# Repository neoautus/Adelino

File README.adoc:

= Adelino
:page-layout: book

O Adelino é uma placa de desenvolvimento baseada no ATmega32U4 com um módulo ESP-12F integrado.
Ela foi inicialmente inspirada no Arduino Leonardo e no Arduino Yún.

Visite nosso https://github.com/neoautus/Adelino/wiki[Wiki] para conhecer melhor este produto!

'''

Adelino is an ATmega32U4 development board with integrated ESP-12F module.
It was initially inspired by Arduino Leonardo and Arduino Yún.

Visit our https://github.com/neoautus/Adelino/wiki[Wiki] for more information!

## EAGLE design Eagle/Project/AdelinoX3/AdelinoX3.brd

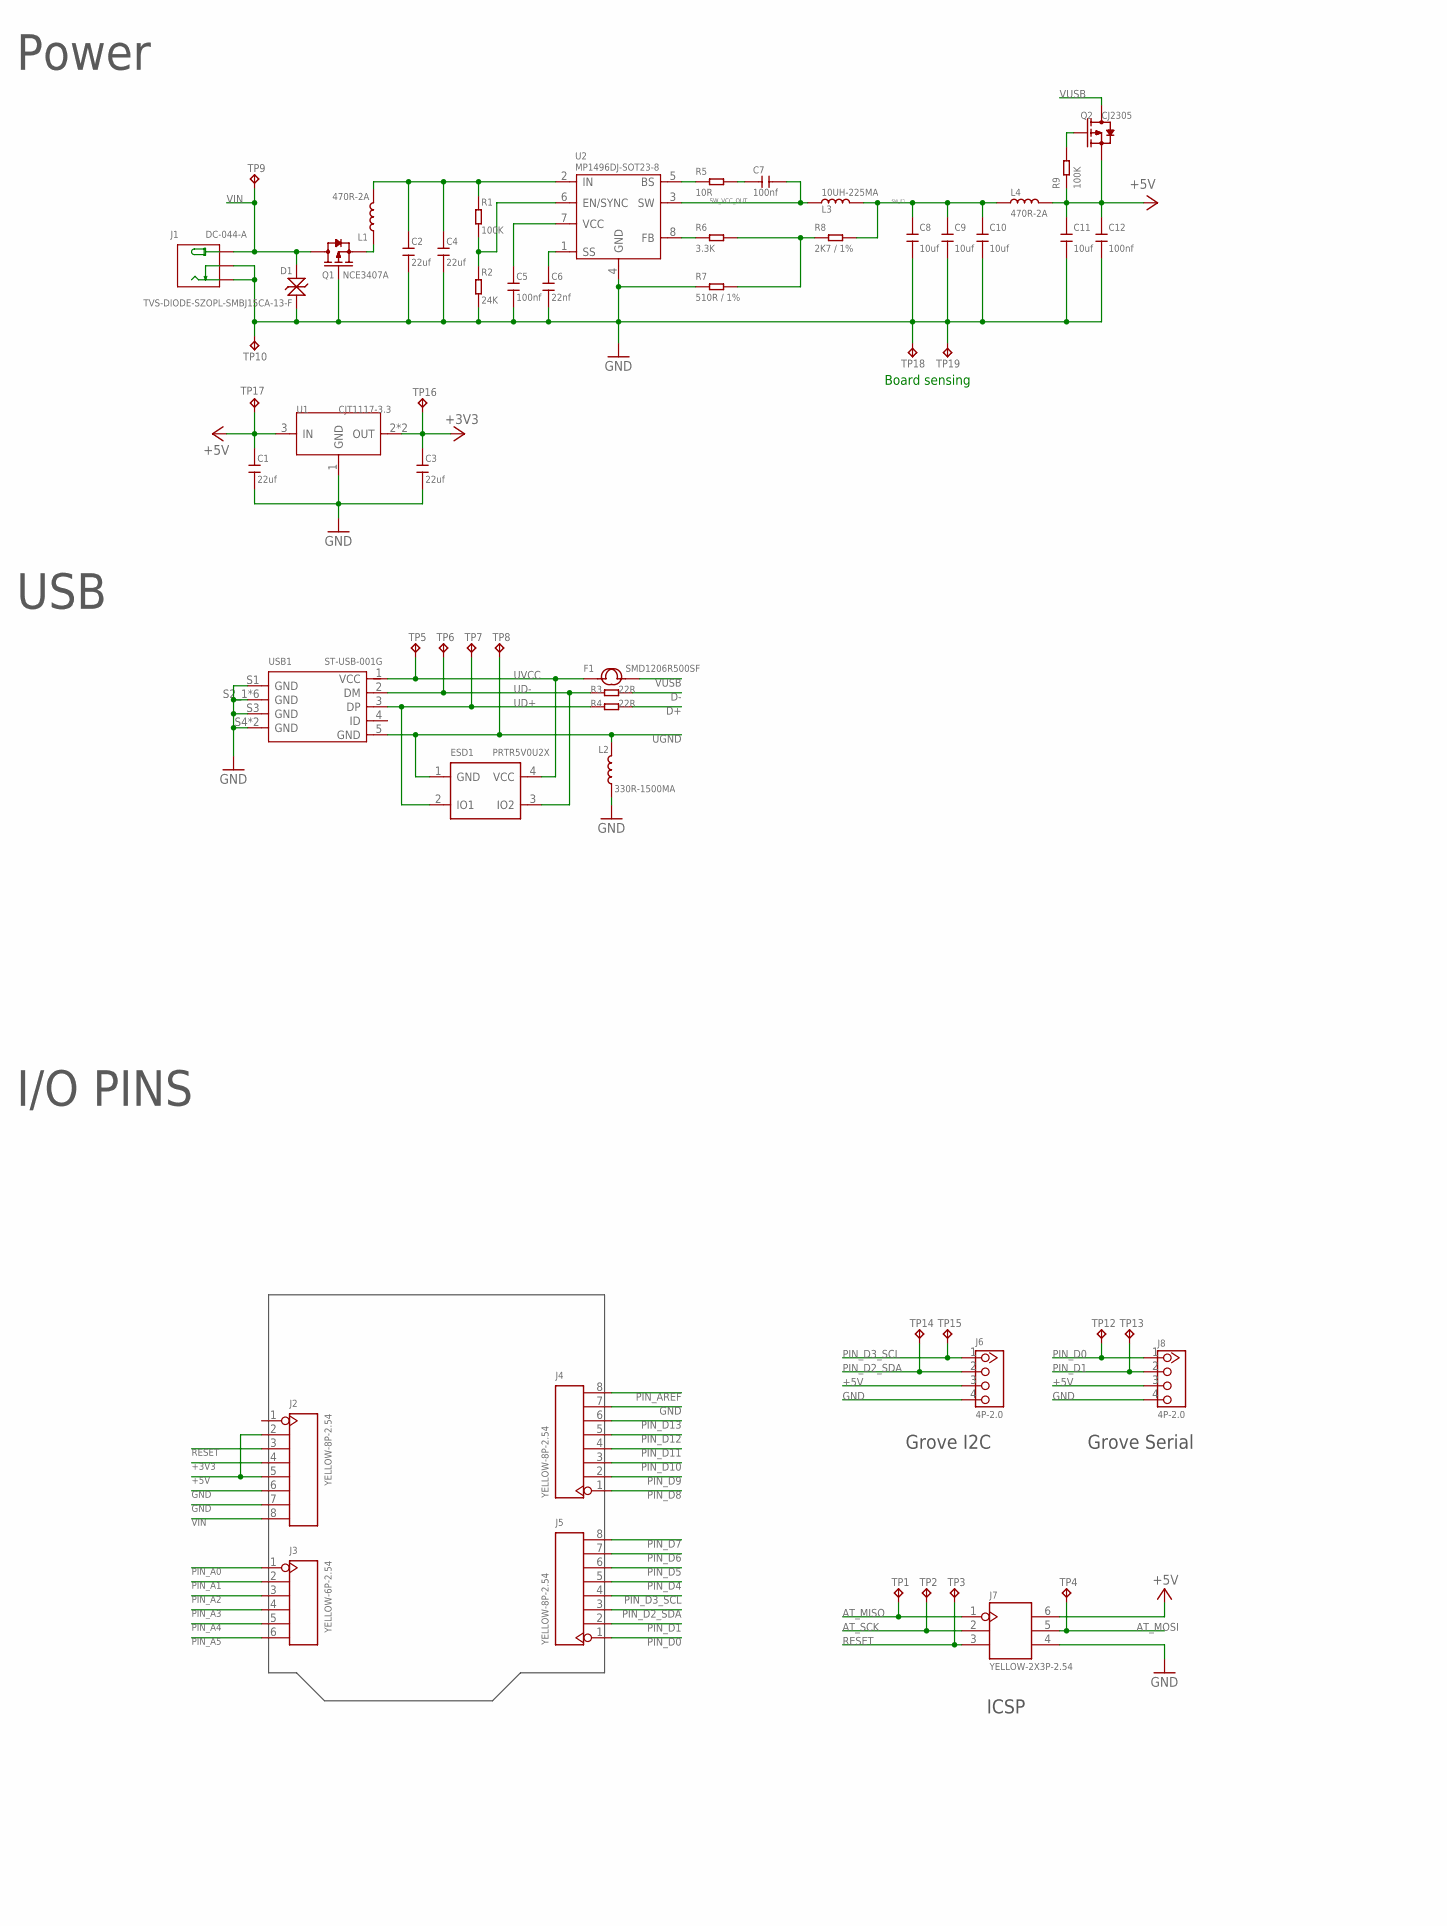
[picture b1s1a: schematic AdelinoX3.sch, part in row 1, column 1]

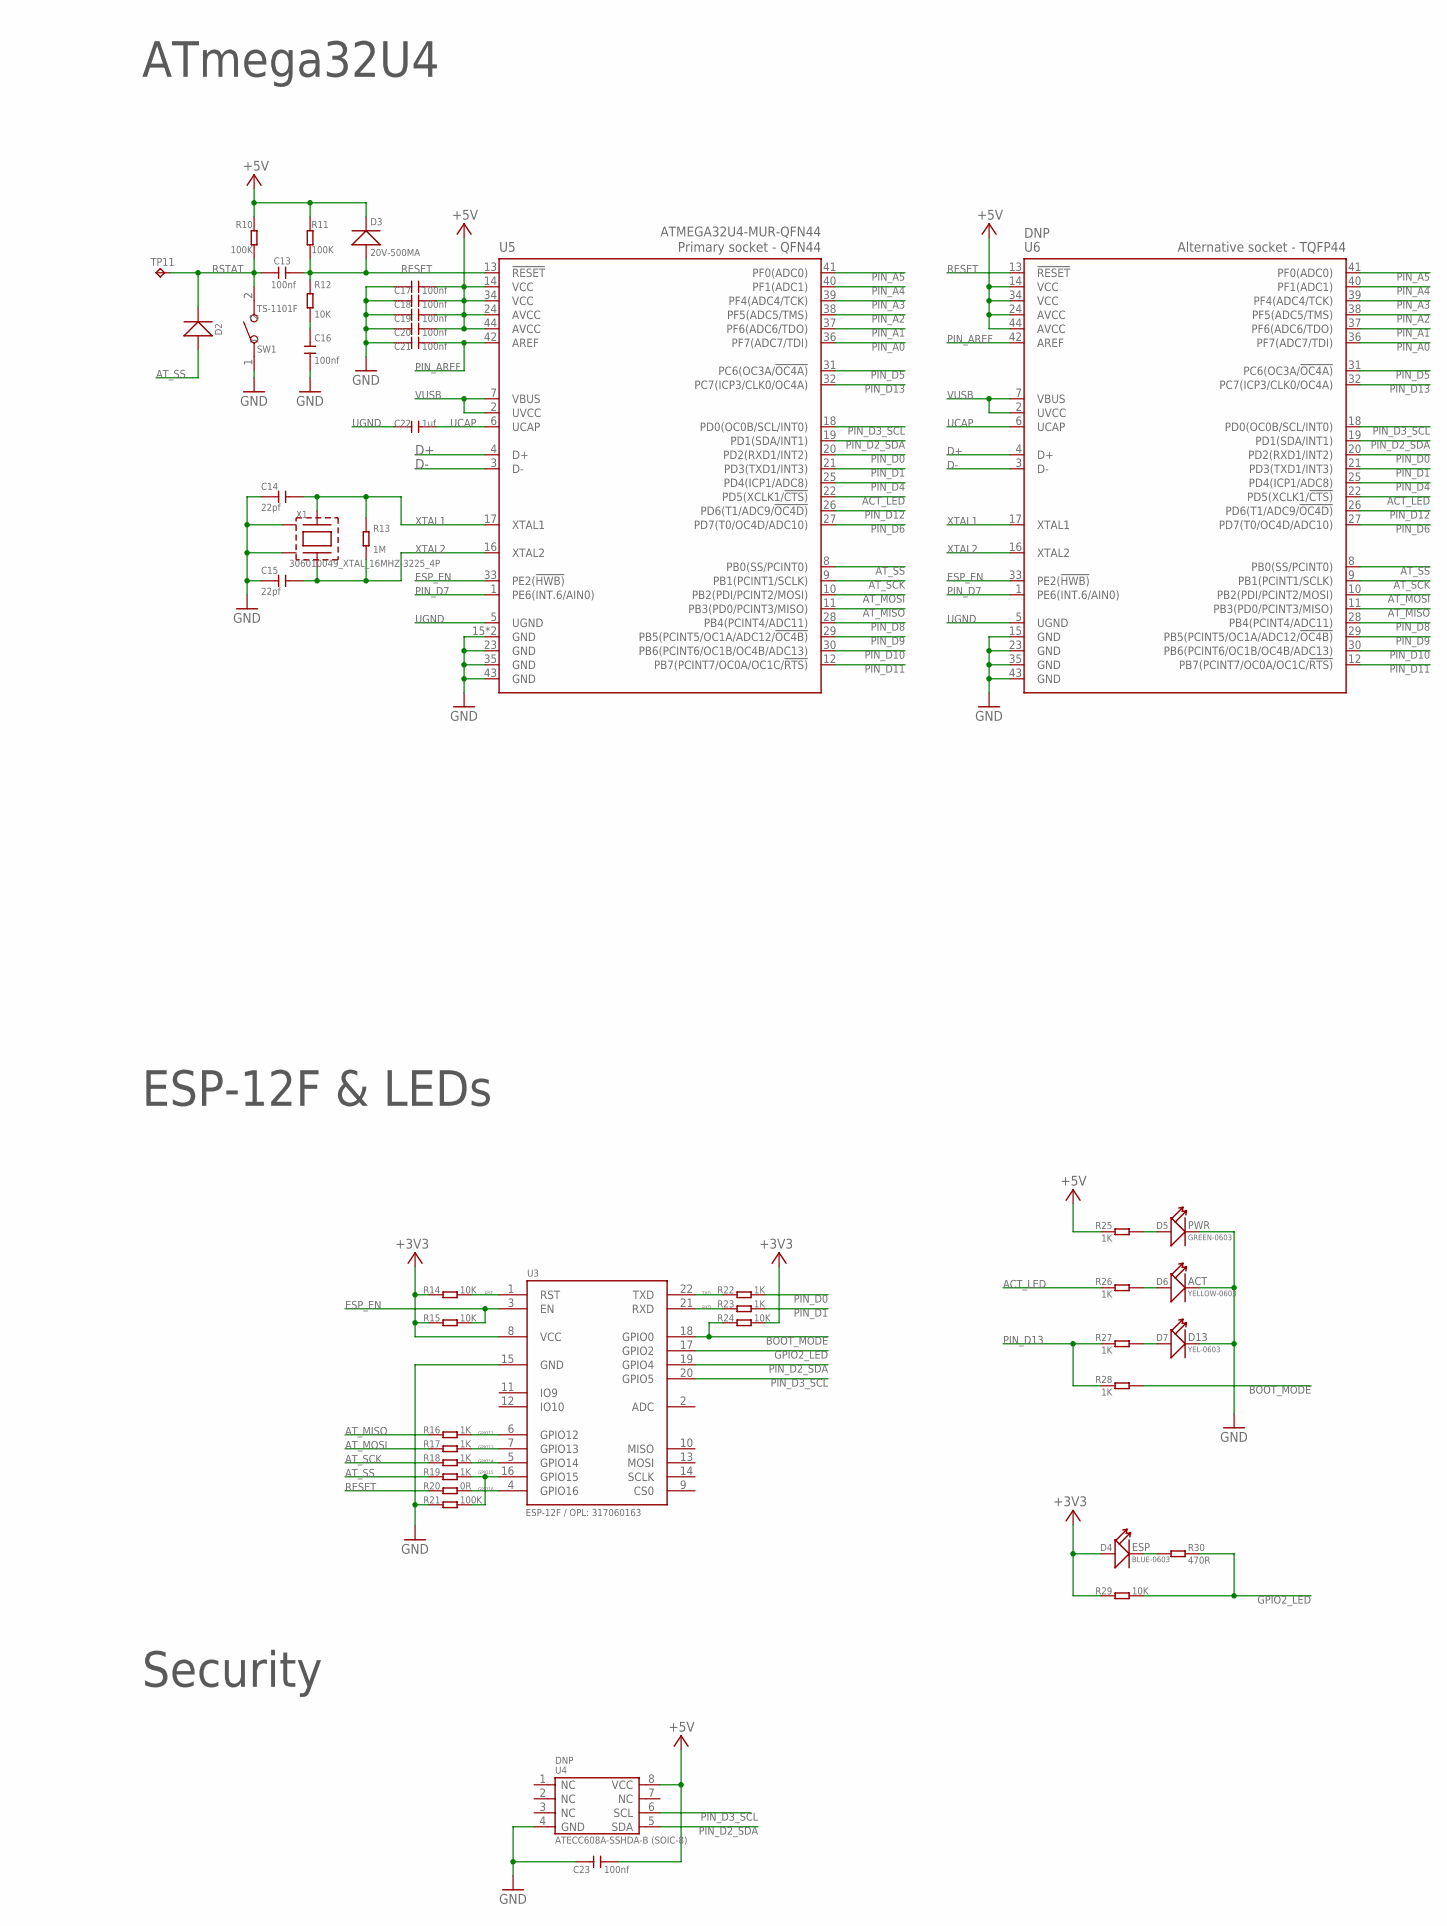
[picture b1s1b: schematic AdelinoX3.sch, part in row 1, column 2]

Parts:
C1, C2, C3, C4: 22uf; C1206
C5, C7, C12, C13, C16, C17, C18, C19, C20, C21, C23: 100nf; C0603
C6: 22nf; C0603
C8, C9, C10, C11: 10uf; C0805
C14, C15: 22pf; C0603
C22: 1uf; C0603
D1: TVS-DIODE-SZOPL-SMBJ15CA-13-F; DO-214AA
D2, D3: 20V-500MA; SOD-123
D4: BLUE-0603; LED-0603
D5: GREEN-0603; LED-0603
D6: YELLOW-0603; LED-0603
D7: YEL-0603; LED-0603
ESD1: PRTR5V0U2X; SOT-143B
F1: SMD1206R500SF; F1206
J1: DC-044-A; DCJ3P-11.6X9.6X7.0MM
J2, J4, J5: YELLOW-8P-2.54; H8-2.54
J3: YELLOW-6P-2.54; H6-2.54
J6, J8: 4P-2.0; HW4-2.0
J7: YELLOW-2X3P-2.54; H2X3-2.54
L1, L4: 470R-2A; L0805
L2: 330R-1500MA; L0805
L3: 10UH-225MA; L5040S
Q1: NCE3407A; SOT-23
Q2: CJ2305; SOT-23
R1, R9, R10, R11, R21: 100K; R0603
R2: 24K; R0603
R3, R4: 22R; R0603
R5: 10R; R0603
R6: 3.3K; R0603
R7: 3K / 1%; R0603
R8: 2K7 / 1%; R0603
R12, R14, R15, R24, R29: 10K; R0603
R13: 1M; R0603
R16, R17, R18, R19, R22, R23, R25, R26, R27, R28: 1K; R0603
R20: 0R; R0603
R30: 470R; R0603
SW1: TS-1101F; SW2-5.0-6.0X3.0X4.3MM
TP1, TP2, TP3, TP4, TP5, TP6, TP7, TP8, TP9, TP10, TP11, TP12, TP13, TP14, TP15, TP16, TP17, TP18, TP19: TPTP16R; TP16R
U1: CJT1117-3.3; SOT-223
U2: MP1496DJ-SOT23-8; SOT-23-8
U3: ESP-12F / OPL: 317060163; ESP-12F
U4: DNP; SOIC8-1.27-5X4MM; MPN ATECC608A-SSHDA-B
U5: ATMEGA32U4-MUR-QFN44; QFN44G-0.5-7X7MM
U6: DNP; TQFP44-0.8-9.6X9.6MM
USB1: ST-USB-001G; MICRO-USB5+4P-SMD-0.65-B
X1: 306010049_XTAL_16MHZ-3225_4P; X3225_4P

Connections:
+3V3: C3.2, D4.+, J2.4, R14.1, R15.1, R24.2, R29.1, TP16.TP, U1.2 (OUT), U1.TER (OUT), U3.8 (VCC)
+5V: C1.2, C11.2, C12.2, C17.1, C18.1, C19.1, C20.1, C23.1, D3.-, J2.2, J2.5, J6.3, J7.6, J8.3, L4.2, Q2.2 (S), R9.1, R10.1, R11.2, R25.1, TP17.TP, U1.3 (IN), U4.8 (VCC), U5.14 (VCC), U5.24 (AVCC), U5.34 (VCC), U5.44 (AVCC), U6.14 (VCC), U6.24 (AVCC), U6.34 (VCC), U6.44 (AVCC)
ACT_LED: R26.1, U5.22 (PD5(XCLK1/!CTS)), U6.22 (PD5(XCLK1/!CTS))
AT_MISO: J7.1, R16.1, TP1.TP, U5.11 (PB3(PD0/PCINT3/MISO)), U6.11 (PB3(PD0/PCINT3/MISO))
AT_MOSI: J7.5, R17.1, TP4.TP, U5.10 (PB2(PDI/PCINT2/MOSI)), U6.10 (PB2(PDI/PCINT2/MOSI))
AT_SCK: J7.2, R18.1, TP2.TP, U5.9 (PB1(PCINT1/SCLK)), U6.9 (PB1(PCINT1/SCLK))
AT_SS: D2.+, R19.1, U5.8 (PB0(SS/PCINT0)), U6.8 (PB0(SS/PCINT0))
BOOT_MODE: R24.1, R28.2, U3.18 (GPIO0)
D+: R4.2, U5.4 (D+), U6.4 (D+)
D-: R3.2, U5.3 (D-), U6.3 (D-)
ESP_EN: R15.2, U3.3 (EN), U5.33 (PE2(!HWB)), U6.33 (PE2(!HWB))
GND: C1.1, C2.1, C3.1, C4.1, C5.1, C6.1, C8.1, C9.1, C10.1, C11.1, C12.1, C14.1, C15.1, C16.2, C17.2, C18.2, C19.2, C20.2, C21.2, C23.2, D1.+, D5.-, D6.-, D7.-, J1.CDN1 (CDN), J1.CDN2 (CDN), J1.CDN3 (CDN), J1.CDN4 (CDN), J1.GND1 (-), J1.GND2 (-), J1.GND3 (-), J1.GND4 (-), J2.6, J2.7, J4.7, J6.4, J7.4, J8.4, L2.1, Q1.1 (G), R2.1, R7.1, R21.1, SW1.1, TP10.TP, TP18.TP, TP19.TP, U1.1 (GND), U2.4 (GND), U3.15 (GND), U4.4 (GND), U5.15 (GND), U5.23 (GND), U5.35 (GND), U5.43 (GND), U5.TAB (GND), U6.15 (GND), U6.23 (GND), U6.35 (GND), U6.43 (GND), USB1.S1 (GND), USB1.S2_1 (GND), USB1.S2_2 (GND), USB1.S2_3 (GND), USB1.S3 (GND), USB1.S4 (GND), USB1.S5_1 (GND), USB1.S5_2 (GND), USB1.S5_3 (GND), USB1.S6 (GND), X1.P$2 (GND1), X1.P$4 (GND2)
GPIO2_LED: R29.2, R30.2, U3.17 (GPIO2)
GPIO12: R16.2, U3.6 (GPIO12)
GPIO13: R17.2, U3.7 (GPIO13)
GPIO14: R18.2, U3.5 (GPIO14)
GPIO15: R19.2, R21.2, U3.16 (GPIO15)
GPIO16: R20.2, U3.4 (GPIO16)
unnamed: Q2.1 (G), R9.2
unnamed: R1.2, R2.2, U2.6 (EN/SYNC)
unnamed: L1.1, Q1.2 (S)
unnamed: C16.1, R12.2
unnamed: C7.2, R5.2
unnamed: R6.2, R7.2, R8.1
PIN_A0: J3.1, U5.36 (PF7(ADC7/TDI)), U6.36 (PF7(ADC7/TDI))
PIN_A1: J3.2, U5.37 (PF6(ADC6/TDO)), U6.37 (PF6(ADC6/TDO))
PIN_A2: J3.3, U5.38 (PF5(ADC5/TMS)), U6.38 (PF5(ADC5/TMS))
PIN_A3: J3.4, U5.39 (PF4(ADC4/TCK)), U6.39 (PF4(ADC4/TCK))
PIN_A4: J3.5, U5.40 (PF1(ADC1)), U6.40 (PF1(ADC1))
PIN_A5: J3.6, U5.41 (PF0(ADC0)), U6.41 (PF0(ADC0))
PIN_AREF: C21.1, J4.8, U5.42 (AREF), U6.42 (AREF)
PIN_D0: J5.1, J8.1, R22.2, TP12.TP, U5.20 (PD2(RXD1/INT2)), U6.20 (PD2(RXD1/INT2))
PIN_D1: J5.2, J8.2, R23.2, TP13.TP, U5.21 (PD3(TXD1/INT3)), U6.21 (PD3(TXD1/INT3))
PIN_D2_SDA: J5.3, J6.2, TP14.TP, U3.19 (GPIO4), U4.5 (SDA), U5.19 (PD1(SDA/INT1)), U6.19 (PD1(SDA/INT1))
PIN_D3_SCL: J5.4, J6.1, TP15.TP, U3.20 (GPIO5), U4.6 (SCL), U5.18 (PD0(OC0B/SCL/INT0)), U6.18 (PD0(OC0B/SCL/INT0))
PIN_D4: J5.5, U5.25 (PD4(ICP1/ADC8)), U6.25 (PD4(ICP1/ADC8))
PIN_D5: J5.6, U5.31 (PC6(OC3A/!OC4A)), U6.31 (PC6(OC3A/!OC4A))
PIN_D6: J5.7, U5.27 (PD7(T0/OC4D/ADC10)), U6.27 (PD7(T0/OC4D/ADC10))
PIN_D7: J5.8, U5.1 (PE6(INT.6/AIN0)), U6.1 (PE6(INT.6/AIN0))
PIN_D8: J4.1, U5.28 (PB4(PCINT4/ADC11)), U6.28 (PB4(PCINT4/ADC11))
PIN_D9: J4.2, U5.29 (PB5(PCINT5/OC1A/ADC12/!OC4B)), U6.29 (PB5(PCINT5/OC1A/ADC12/!OC4B))
PIN_D10: J4.3, U5.30 (PB6(PCINT6/OC1B/OC4B/ADC13)), U6.30 (PB6(PCINT6/OC1B/OC4B/ADC13))
PIN_D11: J4.4, U5.12 (PB7(PCINT7/OC0A/OC1C/!RTS)), U6.12 (PB7(PCINT7/OC0A/OC1C/!RTS))
PIN_D12: J4.5, U5.26 (PD6(T1/ADC9/!OC4D)), U6.26 (PD6(T1/ADC9/!OC4D))
PIN_D13: J4.6, R27.1, R28.1, U5.32 (PC7(ICP3/CLK0/OC4A)), U6.32 (PC7(ICP3/CLK0/OC4A))
RESET: C13.1, D3.+, J2.3, J7.3, R11.1, R12.1, R20.1, TP3.TP, U5.13 (!RESET), U6.13 (!RESET)
RST: R14.2, U3.1 (RST)
RSTAT: C13.2, D2.-, R10.2, SW1.2, TP11.TP
RXD: R23.1, U3.21 (RXD)
SW_BS: R5.1, U2.5 (BS)
SW_F1: C8.2, C9.2, C10.2, L3.2, L4.1, R8.2
SW_FB: R6.1, U2.8 (FB)
SW_SS: C6.2, U2.1 (SS)
SW_VCAP: C5.2, U2.7 (VCC)
SW_VCC_IN: C2.2, C4.2, L1.2, R1.1, U2.2 (IN)
SW_VCC_OUT: C7.1, L3.1, U2.3 (SW)
TXD: R22.1, U3.22 (TXD)
UCAP: C22.2, U5.6 (UCAP), U6.6 (UCAP)
UD+: ESD1.2 (IO1), R4.1, TP7.TP, USB1.3 (DP)
UD-: ESD1.3 (IO2), R3.1, TP6.TP, USB1.2 (DM)
UGND: C22.1, ESD1.1 (GND), L2.2, TP8.TP, U5.5 (UGND), U6.5 (UGND), USB1.5 (GND)
UVCC: ESD1.4 (VCC), F1.1, TP5.TP, USB1.1 (VCC)
VIN: D1.-, J1.VCC1 (+), J1.VCC2 (+), J1.VCC3 (+), J1.VCC4 (+), J2.8, Q1.3 (D), TP9.TP
VUSB: F1.2, Q2.3 (D), U5.2 (UVCC), U5.7 (VBUS), U6.2 (UVCC), U6.7 (VBUS)
XTAL1: C14.2, R13.2, U5.17 (XTAL1), U6.17 (XTAL1), X1.P$1
XTAL2: C15.2, R13.1, U5.16 (XTAL2), U6.16 (XTAL2), X1.P$3
_ACT: D6.+, R26.2
_D13: D7.+, R27.2
_ESP: D4.-, R30.1
_PWR: D5.+, R25.2

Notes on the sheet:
USB
Power
ATmega32U4
ESP-12F & LEDs
I/O PINS
Grove I2C
Grove Serial
Security
ICSP
Board sensing

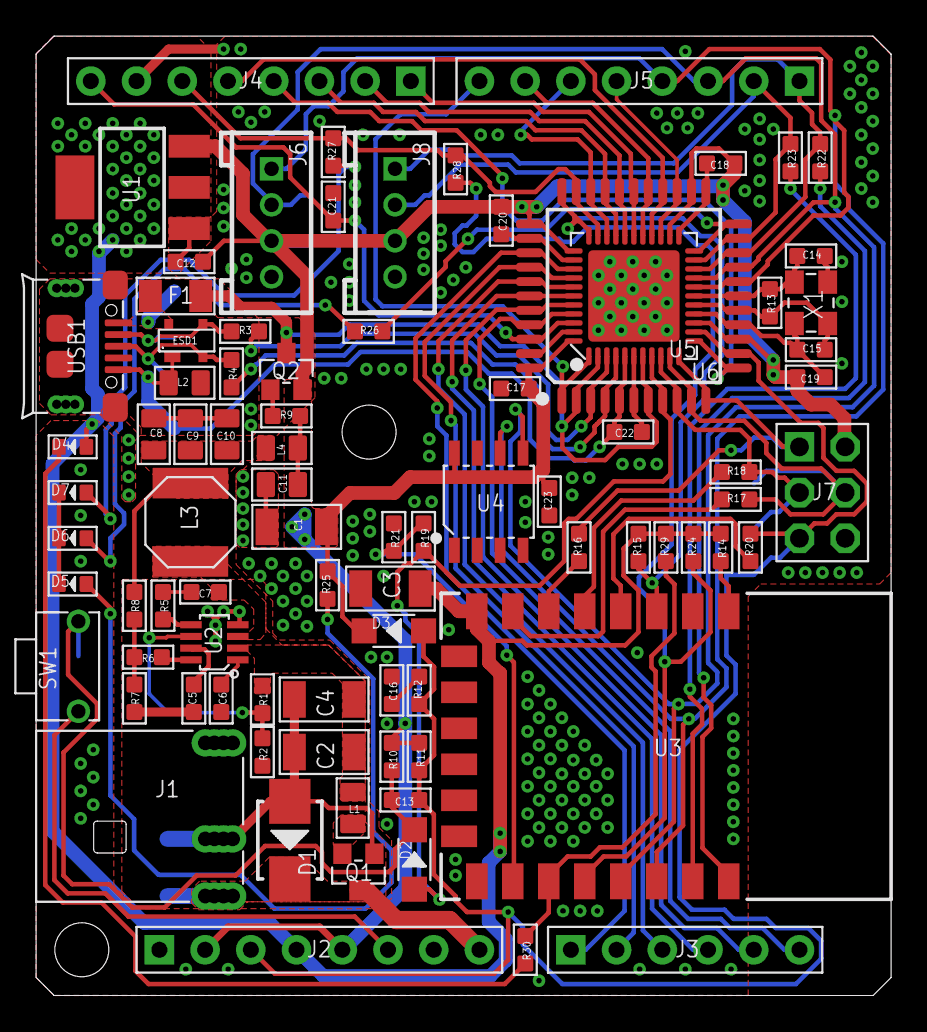
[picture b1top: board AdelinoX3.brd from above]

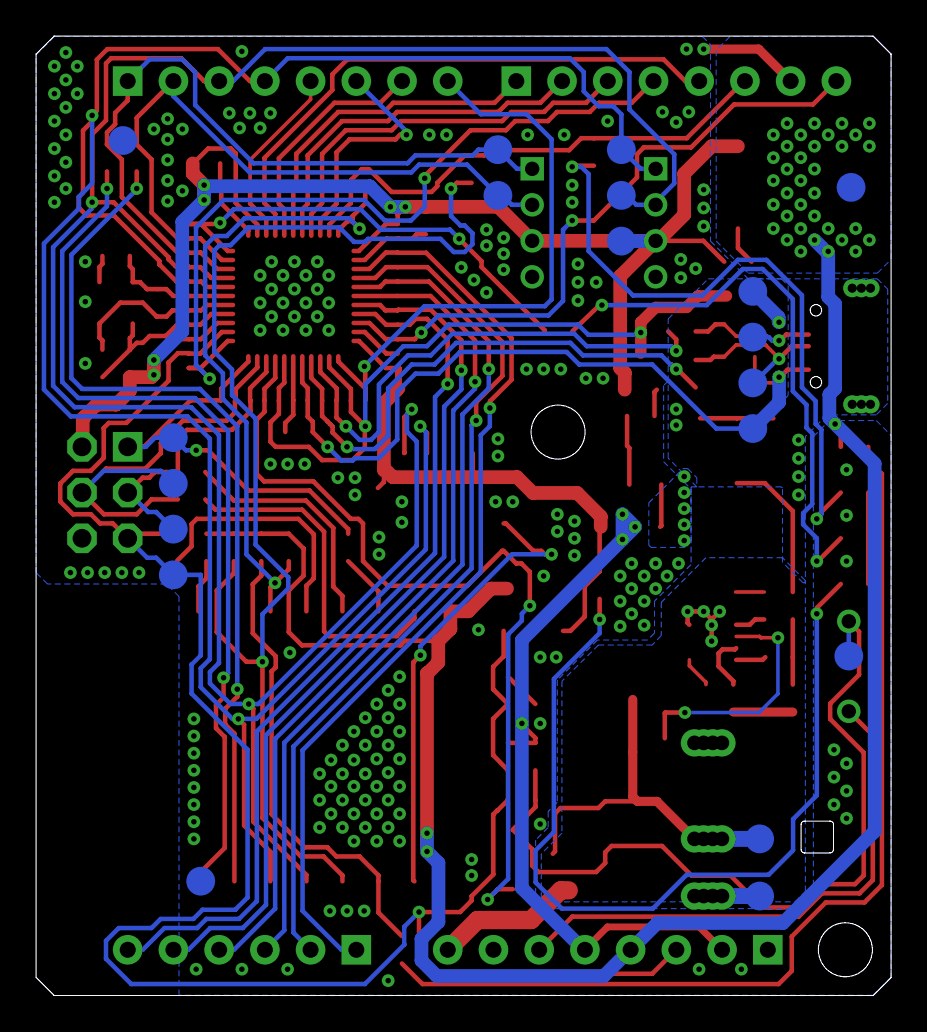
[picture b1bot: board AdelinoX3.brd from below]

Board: 2 copper layers, 47.5 x 53.3 mm, 104 parts (19 on the bottom side), 70 nets.

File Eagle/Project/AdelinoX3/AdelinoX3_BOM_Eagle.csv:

"Qty";"Value";"Device";"Package";"Parts";"Description";"DESC";"LABEL";"MOUSER_REF";"MPN";"R";"SKU";"TP_SIGNAL_NAME";"VALUE";
"1";"0R";"SMD-RES-0R-5%-1/10W(0603)";"R0603";"R20";"301010292";"";"";"";"RC0603JR-070RL";"";"";"";"0R";
"5";"100K";"SMD-RES-100K-5%-1/10W(0603)";"R0603";"R1, R9, R10, R11, R21";"301010089";"";"";"";"RC0603JR-07100KL";"";"";"";"100K 1/10W";
"11";"100nf";"CERAMIC-100NF-50V-10%-X7R(0603)";"C0603";"C5, C7, C12, C13, C16, C17, C18, C19, C20, C21, C23";"302010138";"";"";"";"CC0603KRX7R9BB104";"";"";"";"100nf";
"5";"10K";"SMD-RES-10K-5%-1/10W(0603)";"R0603";"R12, R14, R15, R24, R29";"301010293";"";"";"";"RC0603JR-0710KL";"";"";"";"10K 1/10W";
"1";"10R";"SMD-RES-10R-1%-1/10W(0603)";"R0603";"R5";"301010185";"";"";"";"RC0603FR-0710RL";"";"";"";"10R";
"1";"10UH-225MA";"SMD-INDUCTOR-10UH-20%-2.35A(2P-5X5X4MM)";"L5040S";"L3";"303010147";"";"";"";"";"";"";"";"";
"4";"10uf";"CERAMIC-10UF-25V-10%-X5R(0805)";"C0805";"C8, C9, C10, C11";"302010178";"";"";"";"CC0805KKX5R8BB106";"";"";"";"10uf";
"10";"1K";"SMD-RES-1K-5%-1/10W(0603)";"R0603";"R16, R17, R18, R19, R22, R23, R25, R26, R27, R28";"301010291";"";"";"";"RC0603JR-071KL";"";"";"";"1K 1/10W";
"1";"1M";"SMD-RES-1M-5%-1/10W(0603)";"R0603";"R13";"301010100";"";"";"";"RC0603JR-071ML";"";"";"";"1M 1/10W";
"1";"1uf";"CERAMIC-1UF-25V-10%-X7R(0603)";"C0603";"C22";"302010139";"";"";"";"CC0603KRX7R8BB105";"";"";"";"1uf";
"2";"20V-500MA";"SMD-DIODE-SCHOTTKY-20V-500MA(SOD-123)P";"SOD-123";"D2, D3";"304020028";"";"";"";"MBR0520LT1G";"";"";"";"20V-500MA";
"2";"22R";"SMD-RES-22R-5%-1/10W(0603)";"R0603";"R3, R4";"301010289";"";"";"";"RC0603JR-0722RL";"";"";"";"22R";
"1";"22nf";"CERAMIC-22NF-50V-10%-X7R(0603)";"C0603";"C6";"302010095";"";"";"";"CC0603KRX7R9BB223";"";"";"";"22nf";
"2";"22pf";"CERAMIC-22PF-50V-5%-NPO(0603)";"C0603";"C14, C15";"302010143";"";"";"";"CC0603JRNPO9BN220";"";"";"";"22pf";
"4";"22uf";"CERAMIC-22UF-16V-10%-X7R(1206)";"C1206";"C1, C2, C3, C4";"302010182";"";"";"";"";"";"";"";"";
"1";"24K";"SMD-RES-24K-1%-1/10W(0603)";"R0603";"R2";"301010232";"";"";"";"";"";"";"";"";
"1";"2K7 / 1%";"SMD-RES-2.7K-1%-1/10W(0603)";"R0603";"R8";"301010193";"";"";"";"";"2K7 / 1%";"";"";"";
"1";"3.3K";"SMD-RES-3.3K-5%-1/10W(0603)";"R0603";"R6";"301010112";"";"";"";"";"";"";"";"";
"1";"306010049_XTAL_16MHZ-3225_4P";"306010049_XTAL_16MHZ-3225_4P";"X3225_4P";"X1";"SMD Crystal 16MHz-9pF-10ppm-40R;4P-L3.2*W2.5mm, SKU: 306010049";"";"";"";"";"";"";"";"";
"1";"330R-1500MA";"SMD-FERRITE-BEAD-330R-1500MA(0805)'0805'";"L0805";"L2";"303030006";"";"";"";"BLM21PG331SN1D";"";"";"";"330R-1500MA";
"1";"3K / 1%";"SMD-RES-510R-1%-1/10W(0603)";"R0603";"R7";"301010215";"";"";"";"";"510R / 1%";"";"";"";
"1";"470R";"SMD-RES-470R-5%-1/10W(0603)";"R0603";"R30";"301010088";"";"";"";"RC0603JR-07470RL";"";"";"";"470R";
"2";"470R-2A";"SMD-FERRITE-BEAD-470R-2A(0805)'0805'";"L0805";"L1, L4";"303030008";"";"";"";"WLB2012-471T20";"";"";"";"470R-2A";
"2";"4P-2.0";"GROVE-CONNECTOR-DIP(4P-2.0)";"HW4-2.0";"J6, J8";"320110033";"";"";"";"";"";"";"";"4P-2.0";
"1";"ATMEGA32U4-MUR-QFN44";"MCU-ATMEGA32U4-MUR(VQFN44)";"QFN44G-0.5-7X7MM";"U5";"310010016";"Primary socket - QFN44";"";"";"ATMEGA32U4-MUR";"";"";"";"ATMEGA32U4-MUR-QFN44";
"1";"BLUE-0603";"SMD-LED-CLEAR-BLUE(0603)";"LED-0603";"D4";"304090045";"";"ESP";"";"19-217-BHC-ZL1M2RY-3T";"";"";"";"BLUE-0603";
"1";"CJ2305";"SMD-MOSFET-P-CH-8V-4.1A-CJ2305(SOT-23)";"SOT-23";"Q2";"305030014";"";"";"";"CJ2305";"";"";"";"CJ2305";
"1";"CJT1117-3.3";"PMIC-CJT1117-3.3(SOT223)";"SOT-223";"U1";"310030097";"";"";"";"CJT1117-3.3";"";"";"";"CJT1117-3.3-SOT223";
"1";"DC-044-A";"JACK-DC-044-A";"DCJ3P-11.6X9.6X7.0MM";"J1";"320120002";"";"";"";"JACK-DC-044-A";"";"";"";"DC-044-A";
"1";"DNP";"ATECC608(SOIC8)";"SOIC8-1.27-5X4MM";"U4";"ATECC608";"ATECC608A-SSHDA-B (SOIC-8)";"";"https://www.mouser.com/ProductDetail/556-ATECC608ASSHDAB";"ATECC608A-SSHDA-B";"";"";"";"ATECC608-SOIC8";
"1";"DNP";"MCU-ATMEGA32U4-AU(TQFP44)";"TQFP44-0.8-9.6X9.6MM";"U6";"310010010";"Alternative socket - TQFP44";"";"";"ATMEGA32U4";"";"";"";"ATMEGA32U4-TQFP44";
"1";"ESP-12F / OPL: 317060163";"ESP-12F";"ESP-12F";"U3";"317060163";"";"";"";"";"";"";"";"";
"1";"GREEN-0603";"SMD-LED-CLEAR-GREEN(0603)";"LED-0603";"D5";"304090043";"";"PWR";"";"19-217-G7C-AN1P2-3T";"";"";"";"GREEN-0603";
"1";"MP1496DJ-SOT23-8";"PMIC-MP1496DJ(SOT23-8)";"SOT-23-8";"U2";"310030121";"";"";"";"MP1496DJ";"";"";"";"MP1496DJ-SOT23-8";
"1";"NCE3407A";"SMD-MOSFET-P-CH-VDC=30V-ID=4.3A-NCE3407A(SOT-23)";"SOT-23";"Q1";"305030010";"";"";"";"NCE3407A";"";"";"";"NCE3407A";
"1";"PRTR5V0U2X";"SMD-DIODE-TVS-5.5V";"SOT-143B";"ESD1";"SMD Diode TVS;5.5V";"";"";"";"NXP";"PRTR5V0U2X,215";"";"304050022";"";
"1";"SMD1206R500SF";"SMD-PPTC-500MA(1206)";"F1206";"F1";"307010002";"";"";"";"SMD1206R500SF";"";"";"";"SMD1206R500SF";
"1";"ST-USB-001G";"MICRO-USB-SMD-B-WITHOUT-POST-W/P(ST-USB-001G)";"MICRO-USB5+4P-SMD-0.65-B";"USB1";"320010000";"";"";"";"ST-USB-001G";"";"";"";"ST-USB-001G";
"19";"TPTP16R";"TPTP16R";"TP16R";"TP1, TP2, TP3, TP4, TP5, TP6, TP7, TP8, TP9, TP10, TP11, TP12, TP13, TP14, TP15, TP16, TP17, TP18, TP19";"Test pad";"";"";"";"";"";"";"";"";
"1";"TS-1101F";"DIP-BUTTON(2P-6.0X3.0X4.3MM)-TS-1101F";"SW2-5.0-6.0X3.0X4.3MM";"SW1";"311020025";"";"";"";"TS-1101F";"";"";"";"TS-1101F";
"1";"TVS-DIODE-SZOPL-SMBJ15CA-13-F";"TVS-DIODE-SZOPL-SMBJ15CA-13-F";"DO-214AA";"D1";"SMD Diode TVS 24VWM/38.9VC-600W;DO-214AA(SMB)";"";"";"";"SMBJ15CA-13-F";"";"SHENZHEN-OPL";"TVS DIODE 15VWM 24.4VC SMB";"";
"1";"YEL-0603";"SMD-LED-CLEAR-YELLOW(0603)";"LED-0603";"D7";"304090044";"";"D13";"";"19-217-Y5C-AM1N1VY-3T";"";"";"";"YELLOW-0603";
"1";"YELLOW-0603";"SMD-LED-CLEAR-YELLOW(0603)";"LED-0603";"D6";"304090044";"";"ACT";"";"19-217-Y5C-AM1N1VY-3T";"";"";"";"YELLOW-0603";
"1";"YELLOW-2X3P-2.54";"DIP-YELLOW-MALE-HEADER-VERT(2X3P-2.54)";"H2X3-2.54";"J7";"320020027";"";"";"";"P125-1203A0BS116A2";"";"";"";"YELLOW-2X3P-2.54";
"1";"YELLOW-6P-2.54";"DIP-YELLOW-FEMALE-HEADER-VERT(6P-2.54)";"H6-2.54";"J3";"320030019";"";"";"";"F185-1106A1BSYA3";"";"";"";"YELLOW-6P-2.54";
"3";"YELLOW-8P-2.54";"DIP-YELLOW-FEMALE-HEADER(8P-2.54)";"H8-2.54";"J2, J4, J5";"320030065";"";"";"";"F185-1108A1BSYC1";"";"";"";"YELLOW-8P-2.54";

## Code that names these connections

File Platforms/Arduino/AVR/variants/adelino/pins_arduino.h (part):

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
// Mapping of analog pins as digital I/O
// A6-A11 share with digital pins
#define PIN_A0   (18)
#define PIN_A1   (19)
#define PIN_A2   (20)
#define PIN_A3   (21)
#define PIN_A4   (22)
#define PIN_A5   (23)
#define PIN_A6   (24)
#define PIN_A7   (25)
#define PIN_A8   (26)
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#define PIN_A10  (28)
#define PIN_A11  (29)

static const uint8_t A0 = PIN_A0;
static const uint8_t A1 = PIN_A1;
static const uint8_t A2 = PIN_A2;
static const uint8_t A3 = PIN_A3;
static const uint8_t A4 = PIN_A4;
static const uint8_t A5 = PIN_A5;
static const uint8_t A6 = PIN_A6;	// D4
static const uint8_t A7 = PIN_A7;	// D6
static const uint8_t A8 = PIN_A8;	// D8
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
// ATMEL ATMEGA32U4 / ARDUINO LEONARDO
//
// D0				PD2					RXD1/INT2
// D1				PD3					TXD1/INT3
// D2				PD1		SDA			SDA/INT1
// D3#				PD0		PWM8/SCL	OC0B/SCL/INT0
// D4		A6		PD4					ADC8
// D5#				PC6		???			OC3A/#OC4A
// D6#		A7		PD7		FastPWM		#OC4D/ADC10
// D7				PE6					INT6/AIN0
//
// D8		A8		PB4					ADC11/PCINT4
// D9#		A9		PB5		PWM16		OC1A/#OC4B/ADC12/PCINT5
// D10#		A10		PB6		PWM16		OC1B/0c4B/ADC13/PCINT6
// D11#				PB7		PWM8/16		0C0A/OC1C/#RTS/PCINT7
// D12		A11		PD6					T1/#OC4D/ADC9
// D13#				PC7		PWM10		CLK0/OC4A
//
// A0		D18		PF7					ADC7
// A1		D19		PF6					ADC6
// A2		D20 	PF5					ADC5
// A3		D21 	PF4					ADC4
// A4		D22		PF1					ADC1
// A5		D23 	PF0					ADC0
//
// New pins D14..D17 to map SPI port to digital pins
//
// MISO		D14		PB3					MISO,PCINT3
// SCK		D15		PB1					SCK,PCINT1
// MOSI		D16		PB2					MOSI,PCINT2
// SS		D17		PB0					RXLED,SS/PCINT0
//
// TXLED	D30		PD5					XCK1
// RXLED	D17	    PB0
// HWB				PE2					HWB

// these arrays map port names (e.g. port B) to the
// appropriate addresses for various functions (e.g. reading
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};

const uint8_t PROGMEM digital_pin_to_port_PGM[] = {
	PD, // D0 - PD2
	PD,	// D1 - PD3
	PD, // D2 - PD1
	PD,	// D3 - PD0
	PD,	// D4 - PD4
	PC, // D5 - PC6
	PD, // D6 - PD7
	PE, // D7 - PE6

	PB, // D8 - PB4
	PB,	// D9 - PB5
	PB, // D10 - PB6
	PB,	// D11 - PB7
	PD, // D12 - PD6
	PC, // D13 - PC7

	PB,	// D14 - MISO - PB3
	PB,	// D15 - SCK - PB1
	PB,	// D16 - MOSI - PB2
	PB,	// D17 - SS - PB0

	PF,	// D18 - A0 - PF7
	PF, // D19 - A1 - PF6
	PF, // D20 - A2 - PF5
	PF, // D21 - A3 - PF4
	PF, // D22 - A4 - PF1
	PF, // D23 - A5 - PF0

	PD, // D24 / D4 - A6 - PD4
	PD, // D25 / D6 - A7 - PD7
	PB, // D26 / D8 - A8 - PB4
	PB, // D27 / D9 - A9 - PB5
	PB, // D28 / D10 - A10 - PB6
	PD, // D29 / D12 - A11 - PD6
	PD, // D30 / TX Led - PD5
};

const uint8_t PROGMEM digital_pin_to_bit_mask_PGM[] = {
	_BV(2), // D0 - PD2
	_BV(3),	// D1 - PD3
	_BV(1), // D2 - PD1
	_BV(0),	// D3 - PD0
	_BV(4),	// D4 - PD4
	_BV(6), // D5 - PC6
	_BV(7), // D6 - PD7
	_BV(6), // D7 - PE6

	_BV(4), // D8 - PB4
	_BV(5),	// D9 - PB5
	_BV(6), // D10 - PB6
	_BV(7),	// D11 - PB7
	_BV(6), // D12 - PD6
	_BV(7), // D13 - PC7

	_BV(3),	// D14 - MISO - PB3
	_BV(1),	// D15 - SCK - PB1
	_BV(2),	// D16 - MOSI - PB2
	_BV(0),	// D17 - SS - PB0

	_BV(7),	// D18 - A0 - PF7
	_BV(6), // D19 - A1 - PF6
	_BV(5), // D20 - A2 - PF5
	_BV(4), // D21 - A3 - PF4
	_BV(1), // D22 - A4 - PF1
	_BV(0), // D23 - A5 - PF0

	_BV(4), // D24 / D4 - A6 - PD4
	_BV(7), // D25 / D6 - A7 - PD7
	_BV(4), // D26 / D8 - A8 - PB4
	_BV(5), // D27 / D9 - A9 - PB5
	_BV(6), // D28 / D10 - A10 - PB6
	_BV(6), // D29 / D12 - A11 - PD6
	_BV(5), // D30 / TX Led - PD5
};

const uint8_t PROGMEM digital_pin_to_timer_PGM[] = {
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};

const uint8_t PROGMEM analog_pin_to_channel_PGM[] = {
	7,	// A0				PF7					ADC7
	6,	// A1				PF6					ADC6
	5,	// A2				PF5					ADC5
	4,	// A3				PF4					ADC4
	1,	// A4				PF1					ADC1
	0,	// A5				PF0					ADC0
	8,	// A6		D4		PD4					ADC8
	10,	// A7		D6		PD7					ADC10
	11,	// A8		D8		PB4					ADC11
	12,	// A9		D9		PB5					ADC12
	13,	// A10		D10		PB6					ADC13
	9	// A11		D12		PD6					ADC9
};

#endif /* ARDUINO_MAIN */
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
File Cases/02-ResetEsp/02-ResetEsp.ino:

// Reset ESP-8266 using HWB.
// 
// It uses reset switch status to decide whether it will
// reset ESP or not. To test, press Adelino reset switch. 
// The sketch will blink 3 times before acquiring the reset 
// switch status. If the reset switch is kept pressed, the
// ESP-8266 will be reset by asserting HWB/PE2 low for 10ms.

int rstat ()
{
  // Read the reset switch preserving the port configuration afterwards
  unsigned char save_DDRD = DDRD;
  unsigned char save_PORTD = PORTD;
  cli ();
  DDRD &= ~_BV(5); // PD5 -> input
  PORTD |= _BV(5); // Pull up
  int stat = !(PIND & _BV(5));
  PORTD = save_PORTD;
  DDRD = save_DDRD;
  sei ();
  return (stat);
}

// Set the logic level on CHIP_EN line, which is 
// connected to HWB (PE2) from ATmega32U4.
int espen (int level)
{
  if (level)
  {
    PORTE |= _BV(2); // PE2 => HIGH
  }
  else
  {
    PORTE &= ~_BV(2); // PE2 => LOW
  }

  // We set pin direction only after setting value
  // because if it's not configured yet (hi-z) it 
  // will be pulled up. If we are setting it HIGH
  // and configure direction first, we may get a
  // unintended short LOW pulse. Therefore, 
  // direction is set only after the intended level 
  // is set.
  DDRE |= _BV(2); // PE2 => OUTPUT
}

void setup ()
{
  // GPIO15 is also HSPI_CS, which is connected to SS on
  // AVR SPI; so we MUST ensure GPIO15 LOW for proper boot.
  pinMode (PIN_SPI_SS, OUTPUT);

  // D13 is also used to drive GPIO0, which is the main
  // boot mode selector. GPIO0 HIGH for normal boot, GPIO0
  // LOW to enter ROM bootloader.
  pinMode (LED_BUILTIN, OUTPUT);

  for (int i = 0; i < 3; i++)
  {
    digitalWrite (LED_BUILTIN, HIGH);
    delay(500);
    digitalWrite (LED_BUILTIN, LOW);
    delay(500);
  }

  //===========
  // Reset ESP
  //===========

  if (rstat ())
  {
    // Enter ROM bootloader
    digitalWrite (LED_BUILTIN, LOW); // GPIO0 => LOW
  }
  else
  {
    // Normal boot
    digitalWrite (LED_BUILTIN, HIGH); // GPIO0 => HIGH
  }
  
  digitalWrite (PIN_SPI_SS, LOW); // GPIO15 => LOW
  delay (10);
  espen (LOW); // CHIP_EN => LOW
  delay (50);
  espen (HIGH); // CHIP_EN => HIGH
  delay (250);
}

void loop ()
{
  // put your main code here, to run repeatedly
}

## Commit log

2018-10-02 Add .gitignore for Eagle backup files.
2018-10-02 Add Seeedstudio OPL library.
2018-10-02 Add Adelino R1 schematics (wip).
2018-10-03 ATmega32u4 wiring and some pinouts.
2018-10-03 Arduino-compatible pinout.
2018-10-03 Add technical refs; ESP8266 wip.
2018-10-04 Base circuit finished; ERC pass.
2018-10-05 Fix R7 too strong pull-up for GPIO0.
2018-10-11 Add design notes from Atmel.
2018-10-11 Change reset switch to be readable.
2018-10-14 Adelino X1 prototype pending revision.
2018-10-15 Add MOSI->GPIO0 connection.
2018-10-15 Add reset switch test case.
2018-10-15 Add ESP reset using SCK.
2018-10-16 Renumbered parts.
2018-10-16 Add ESP-12F module datasheet.
2018-10-16 Now SCK drives CHIP_EN instead of RST; RST pulled high using 4K7.
2018-10-17 Add utility files from Seeedstudio.
2018-10-17 Change ACT_LED to PB0; change ESP_EN to PD5; change WIFI led to GPIO2.
2018-10-18 Adelino X1 final design.
2018-10-18 Add spare vias for SPI.
2018-11-05 Add Coraline bootloader wip.
2018-11-12 Fix component names placement for assembly.
2018-11-13 Fix J1 DC-044 pin drilling; fix J7 dip male header 2X3P pin diameter.
2018-11-13 Fix J1 DC-044 pin drilling; fix J7 dip male header 2X3P pin diameter; get rid of bogus wire stubs.
2018-11-20 Adelino R2 wip.
2018-11-20 Add alternative TQFP44 socket alongside QFN44.
2018-11-20 Getting proper double-socket pairing; minor tweaks.
2018-11-20 Double socket TQFP44+QFN44 finished.
2018-11-29 Power supply routing wip.
2018-11-29 Add ESP-12F datasheet and ANATEL certification.
2018-12-01 Add utility script to burn bootloader.
2018-12-01 Fix USB connector D+/D- wiring.
2018-12-02 Present Adelino X1 to the world :)
2018-12-03 Add useful default port /dev/ttyACM0.
2018-12-03 Add revision 2B preserving TX/RX led compatibility.
2018-12-04 Update GPIO0 wires.
2018-12-04 Remove redundant resistor from GPIO0 wiring.
2018-12-04 Add TVS to protect power input.
2018-12-04 Test changes on reset switch reading.
2018-12-04 Wip.
2018-12-04 Adding native SPI support.
2018-12-05 ATmega/Esp control pins reviewed.
2018-12-05 Reserve resistor for GPIO16/RESET.
2018-12-05 Add nice ESP-12F pinout diagram.
2018-12-05 Add '8266 is 5V tolerant' reference link.
2018-12-07 Adjust drill position.
2018-12-10 Routing wip.
2018-12-10 Add Pacific Open Source Hardware logo.
2018-12-11 Add ECC608 crypto datasheet.
2018-12-12 Fix DC-044-A footprint.
2018-12-12 Add updated Seeedstudio OPL libraries.
2018-12-12 Add MP1496 datasheet.
2018-12-13 Add Adelino-Misc library with ATECC608.
2018-12-13 Add ATECC608 crypto chip; routing wip.
2018-12-17 Add decoupling cap for ECC608.
2018-12-18 Routing wip and DRC.
2018-12-18 Base X2 routing finished.
2018-12-18 Routing revision wip.
2018-12-18 Add Adelino X2 schematics.
2018-12-18 Link schematics directly to raw png file.
2018-12-20 Reset status updated to use Adelino X2 port PD5.
2018-12-22 Add 15V TVS from Shenzhen OPL.
2018-12-24 Route 3.3V decoupling caps away from ESP-12F.
2018-12-26 Added assembly placement.
2018-12-26 Pacific Open Source Hardware => Pacific Open Hardware.
2019-01-03 Add intermediate firmware files to .gitignore.
2019-01-03 Renaming bootloader Coraline to Adelino.
2019-01-03 Adelino is the new official bootloader name.
2019-01-04 Update readme and X2 schematics png.
2019-01-04 Rename bootloader name to 'Adelino'.
    Notice: while this script automatically downloads and extracts LUFA into the proper location, an actual copy of the LUFA library is already included into this repository.
2019-01-04 ResetEsp test case working with Adelino X2.
2019-01-04 Add testcase for ESP-AVR SPI high speed bridge.
2019-01-05 New feature: hold reset for 2 seconds to stay in programming mode (or: do not start sketch); Update ACT led to PD5; Add cylon breathing effect.
2019-01-05 Adopt valid USB VID/PID provided by Microchip Inc.
2019-01-08 Add I2C scan test case for AVR.
2019-01-08 Add I2C scan test case for ESP.
2019-01-10 Add DNP for 32U4 TQFP and ECC608; add some silk art for Adelino X2.
2019-01-10 Adelino X2 bmp art for Eagle import.
2019-01-10 Add Adelino X2 silkscreens and component position cues.
2019-01-10 Better directory structure plus cleanup.
2019-01-11 Little improvements for Assembly Drawing gerber.
2019-01-11 Added gerber files and BOM for SeeedStudio PCBA.
2019-01-11 Update Adelino X2 SCH and BRD quick looks.
2019-01-11 Bootloader went through low carb diet and got 582 bytes lighter :)
2019-01-14 Fix linux usb stack mess with changing VID/PIDs; reformat source; the byte diet continues.
2019-01-15 Add Linux udev rule to avoid ModemManager scanning.
2019-01-15 Change TIMER1 ticks interval from 1ms to 40ms.
2019-01-16 Preparing pcb for Revision A.
2019-01-16 Better ground plane polygon, avoiding swps areas.
2019-01-17 PCBA files for Adelino X2 rev A candidate.
2019-01-25 Update BOM; reposition some component labels.
2019-01-28 Preparing USART0 I/O; fix esptool.py RTS reset error; add ESP reset.
2019-01-30 Adelino X2 PCB just arrived.
2019-01-30 Adelino X2 PCBs just arrived.
2019-01-30 Added support for Bootloader Modes.
2019-02-01 Add support for ESP8266 programming built into bootloader.
2019-02-01 Better GPIO0 sync during ESP8266 reset.
2019-02-03 Fix receive logic within ISR; miscelaneous size optimizations and a simplified 256-byte ring buffer.
2019-02-08 Adding embedded USB/Serial capability for things like MicroPython or NodeMCU.
2019-02-08 Fix misplaced timeout; misc cleaning.
2019-02-08 Add NodeMCU binaries for testing purposes.
2019-02-10 Preliminary files for Arduino's Board Manager.
2019-02-11 Add Adelino's package index for Arduino platform.
2019-02-11 Prepare platform json to become template.
2019-02-11 Use build.sh to create package files.
2019-02-11 Adelino AVR platform support.
2019-02-11 Adelino ESP8266 platform support.
2019-02-11 Package index file for Arduino Platform.
2019-02-13 Adelino alive and breathing :)
2019-03-07 Use adelino.cc servers.
2019-03-20 Discard small capacitance from D5.
2019-03-26 Add Adelino X2 picture.
2019-04-01 Start X3 revision, mostly 0402->0603.
2019-04-01 Wip; use same parts as Seeeduino for SPS.
2019-04-01 Schematic changes to 0603 done.
2019-04-15 First X3 routing finished.
2019-04-15 Routing review in progress.
2019-04-16 Routing review finished.
2019-04-17 Board review 1 (ground plane).
2019-04-18 Board review 2 (vias and silk).
2019-04-19 Fix polygon instead of wire on +5V root.
2019-04-19 Add Adelino qrcode and proper brazilian flag proportions.
2019-04-19 Parts renumbered; tidy up silkscreen.
2019-04-20 Add NetBeans 8.2 project definition.
2019-04-20 Add NetBeans ignore files.
2019-04-20 Fix Makefile to UTF-8.
2019-04-22 Add sensing pads; close vias; better test pad spacing.
2019-04-22 Change bitmaps resolution to be more compatible.
2019-04-22 Adjust Assembly Drawing layer to matching type.
2019-04-22 Add Eagle and Seeed BOM files.
2019-04-22 Add gerber files for Adelino X3.
2019-04-28 Add reference for ESP8266 5V tolerance declaration from Teo Swee Ann.
2019-04-28 Fix via sizes.
2019-04-30 Upgrade ESP8266 toolchain to 2.5.0.
2019-05-14 Fix swapped Grove I2C and UART.
2019-05-14 Add ATmega32U4 pinout diagram.
2019-09-12 Add 32u4 default DFU hex file and restore-to-factory.sh script.
2021-05-30 Use optimal bundled library names
    When multiple libraries contain files matching an #include directive in the program, the Arduino build system must pick
    one to use for compilation. Multiple factors are used in order to make an intelligent determination of which library is
    best.
    In order to enhance this determination, the closeness of match between the library.properties name value and the
    filename in the #include directive is being added as one of those factors. This new factor is referred to as
    "Library Name Priority".
2023-06-04 Ignorar arquivos .DS_Store.
2023-06-04 Adicionadas fotos dos Adelinos do LabMaker PTI.
2023-06-05 Foto do primeiro lote de Adelinos X3.
2023-06-05 Update README.adoc
    Link para o Wiki.
2023-06-05 Imagem do RedFi instalado.
2023-06-05 Adicionada imagem do produto RedFi.
2023-06-05 Adicionado vídeo do Adelino para Centelha.
2023-06-05 Capa do vídeo do Centelha.
2023-06-05 Close-up do Adelino feito no Labmaker.
2023-06-05 Festa dos Adelinos do Labmaker.
2023-06-05 Primeiro protótipo do Adelino.
2023-06-05 Patches do Adelino X1.
2023-06-05 Circuito de reset por pulso.

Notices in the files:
Platforms/Arduino/AVR/variants/adelino/pins_arduino.h:
Copyright (c) 2007 David A. Mellis
Public License along with this library; if not, write to the
Free Software Foundation, Inc., 59 Temple Place, Suite 330,
Boston, MA  02111-1307  USA
